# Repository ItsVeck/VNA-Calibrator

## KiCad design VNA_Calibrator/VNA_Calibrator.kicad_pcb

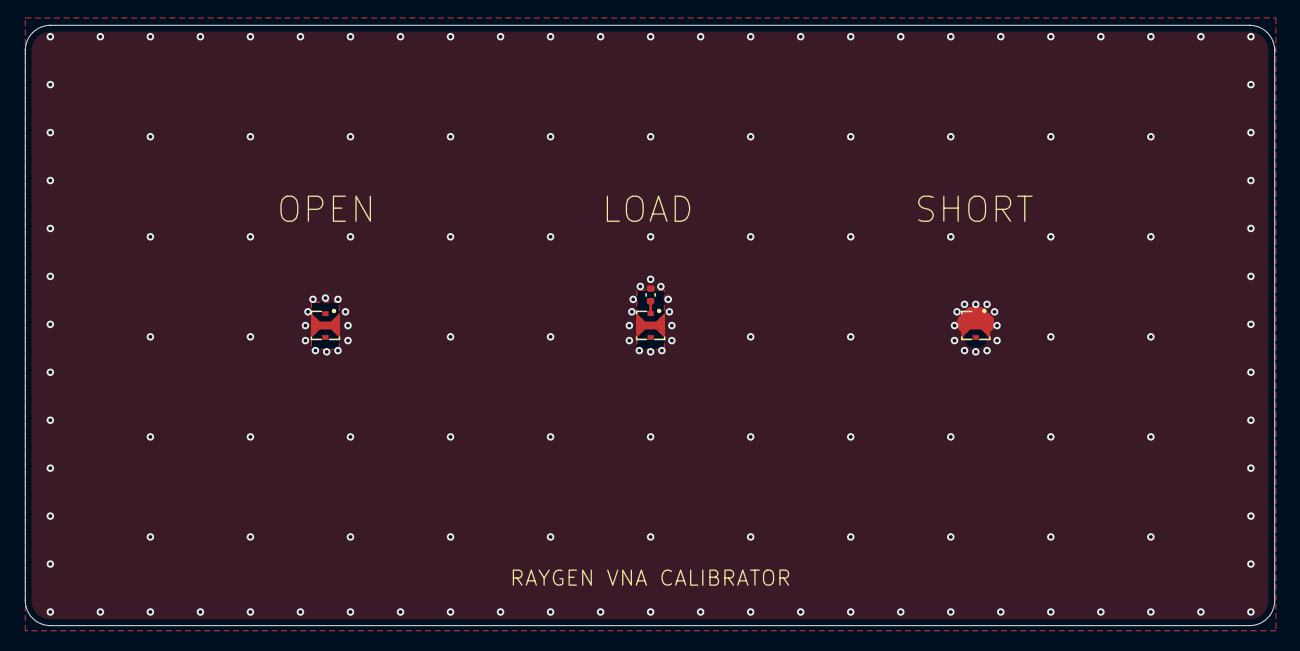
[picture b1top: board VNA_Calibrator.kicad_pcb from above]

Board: 4 copper layers, 99.9 x 48.0 mm, 4 parts (0 on the bottom side), 2 nets.

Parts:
J1, J2, J3: Conn_Coaxial_Switched; Murata_MM8030_2610_Custom
R1: R1; R_0402_1005Metric_Custom

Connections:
GND: J1.1 (In), J1.3 (GND), J2.3 (GND), J3.3 (GND), R1.2
unnamed: J3.1 (In), R1.1

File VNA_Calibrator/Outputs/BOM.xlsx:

| Designator | Qty | Manufacturer | Part Number | Description | Alternative Part (Choose whatever is available)
 | J1, J2, J3 | 3 | Murata | MM8030-2610RK0 | Switching Coax connector | -
 | R1 | 1 | YAGEO | RT0402BRE0750RL | 50R 0.1% Thin Film Resistor, 0402 | FC0402E50R0BST1
